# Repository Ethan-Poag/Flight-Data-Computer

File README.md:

# Flight-Data-Computer
An easy to build open source alternative to the ASA CX-3 aviation data computer.

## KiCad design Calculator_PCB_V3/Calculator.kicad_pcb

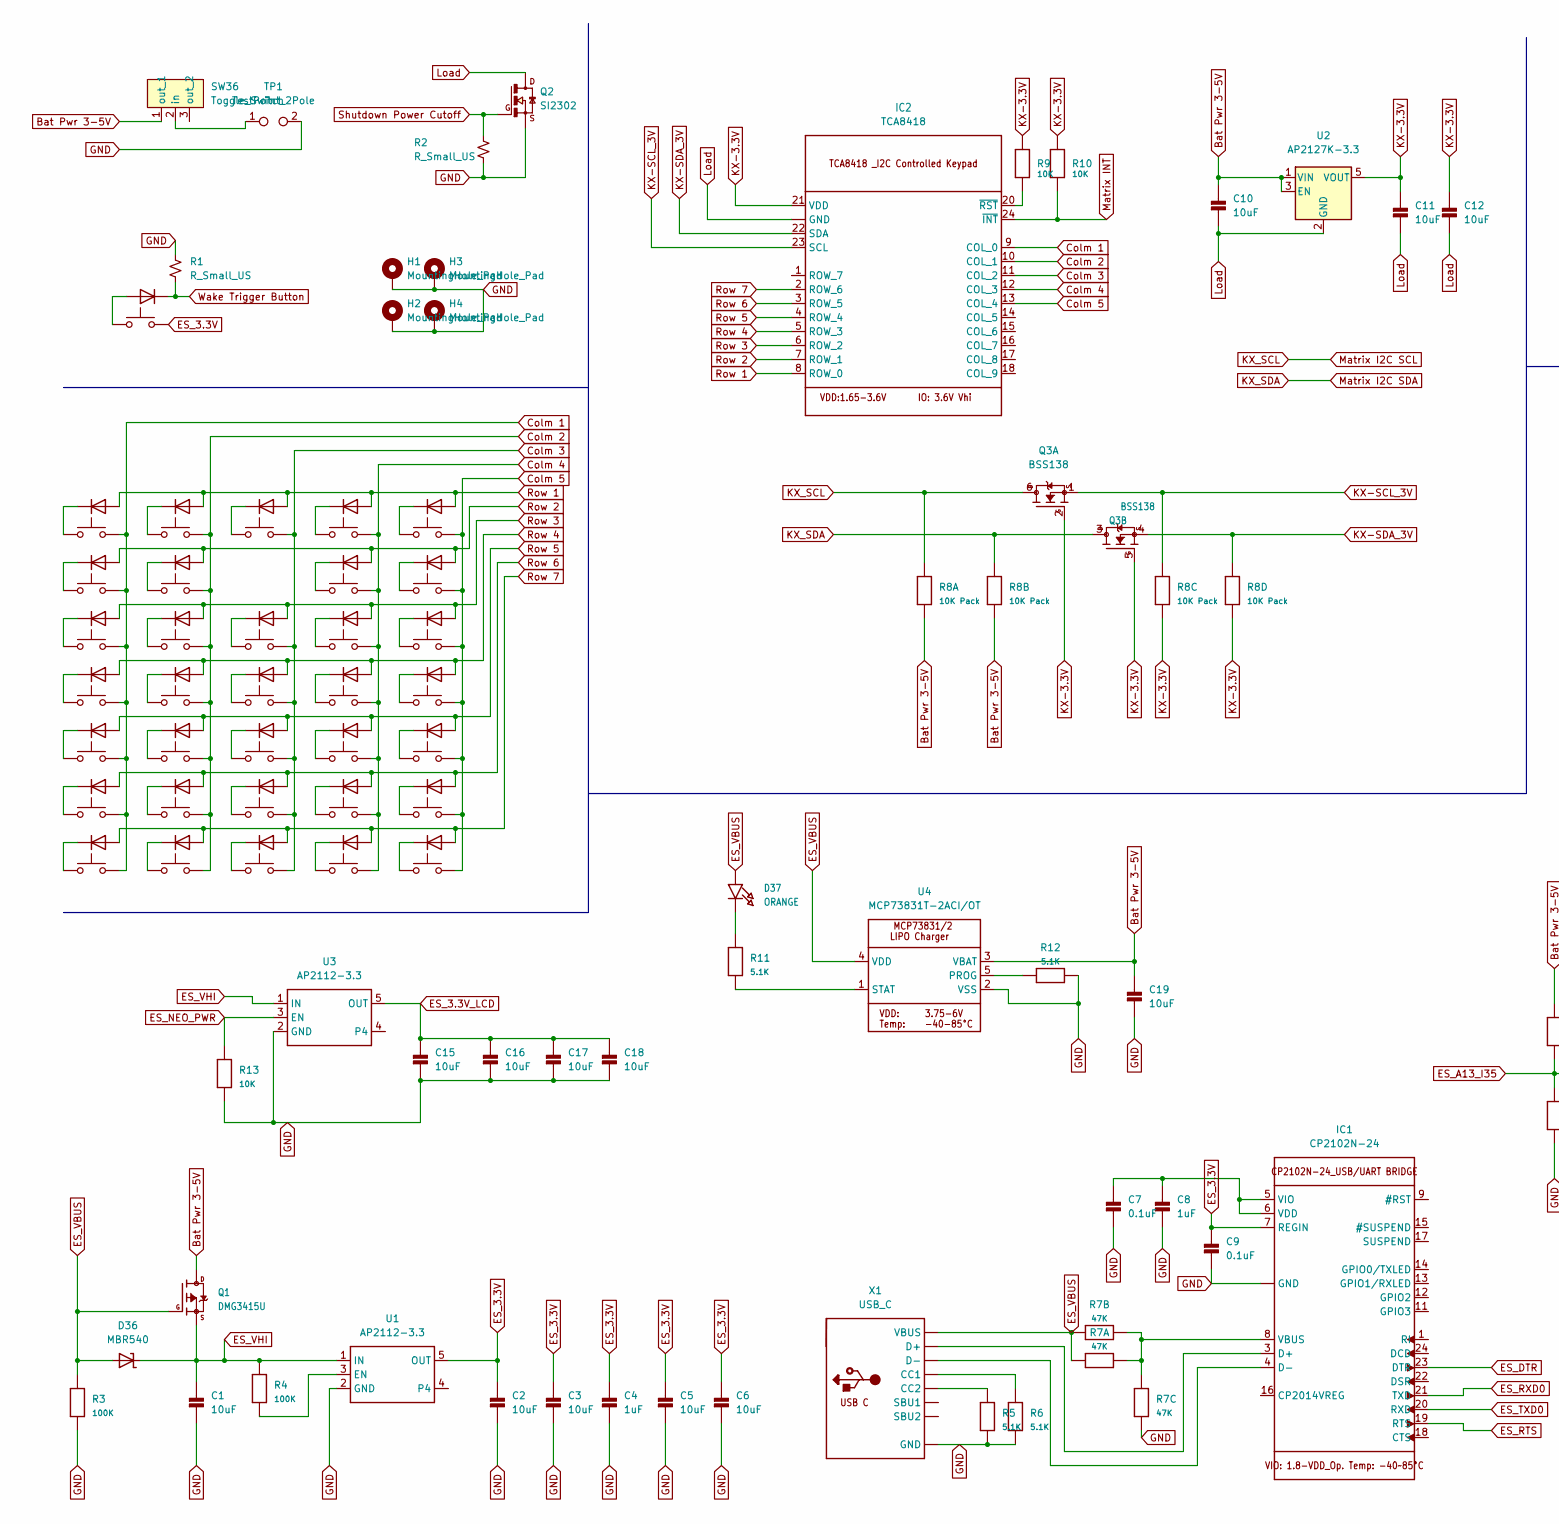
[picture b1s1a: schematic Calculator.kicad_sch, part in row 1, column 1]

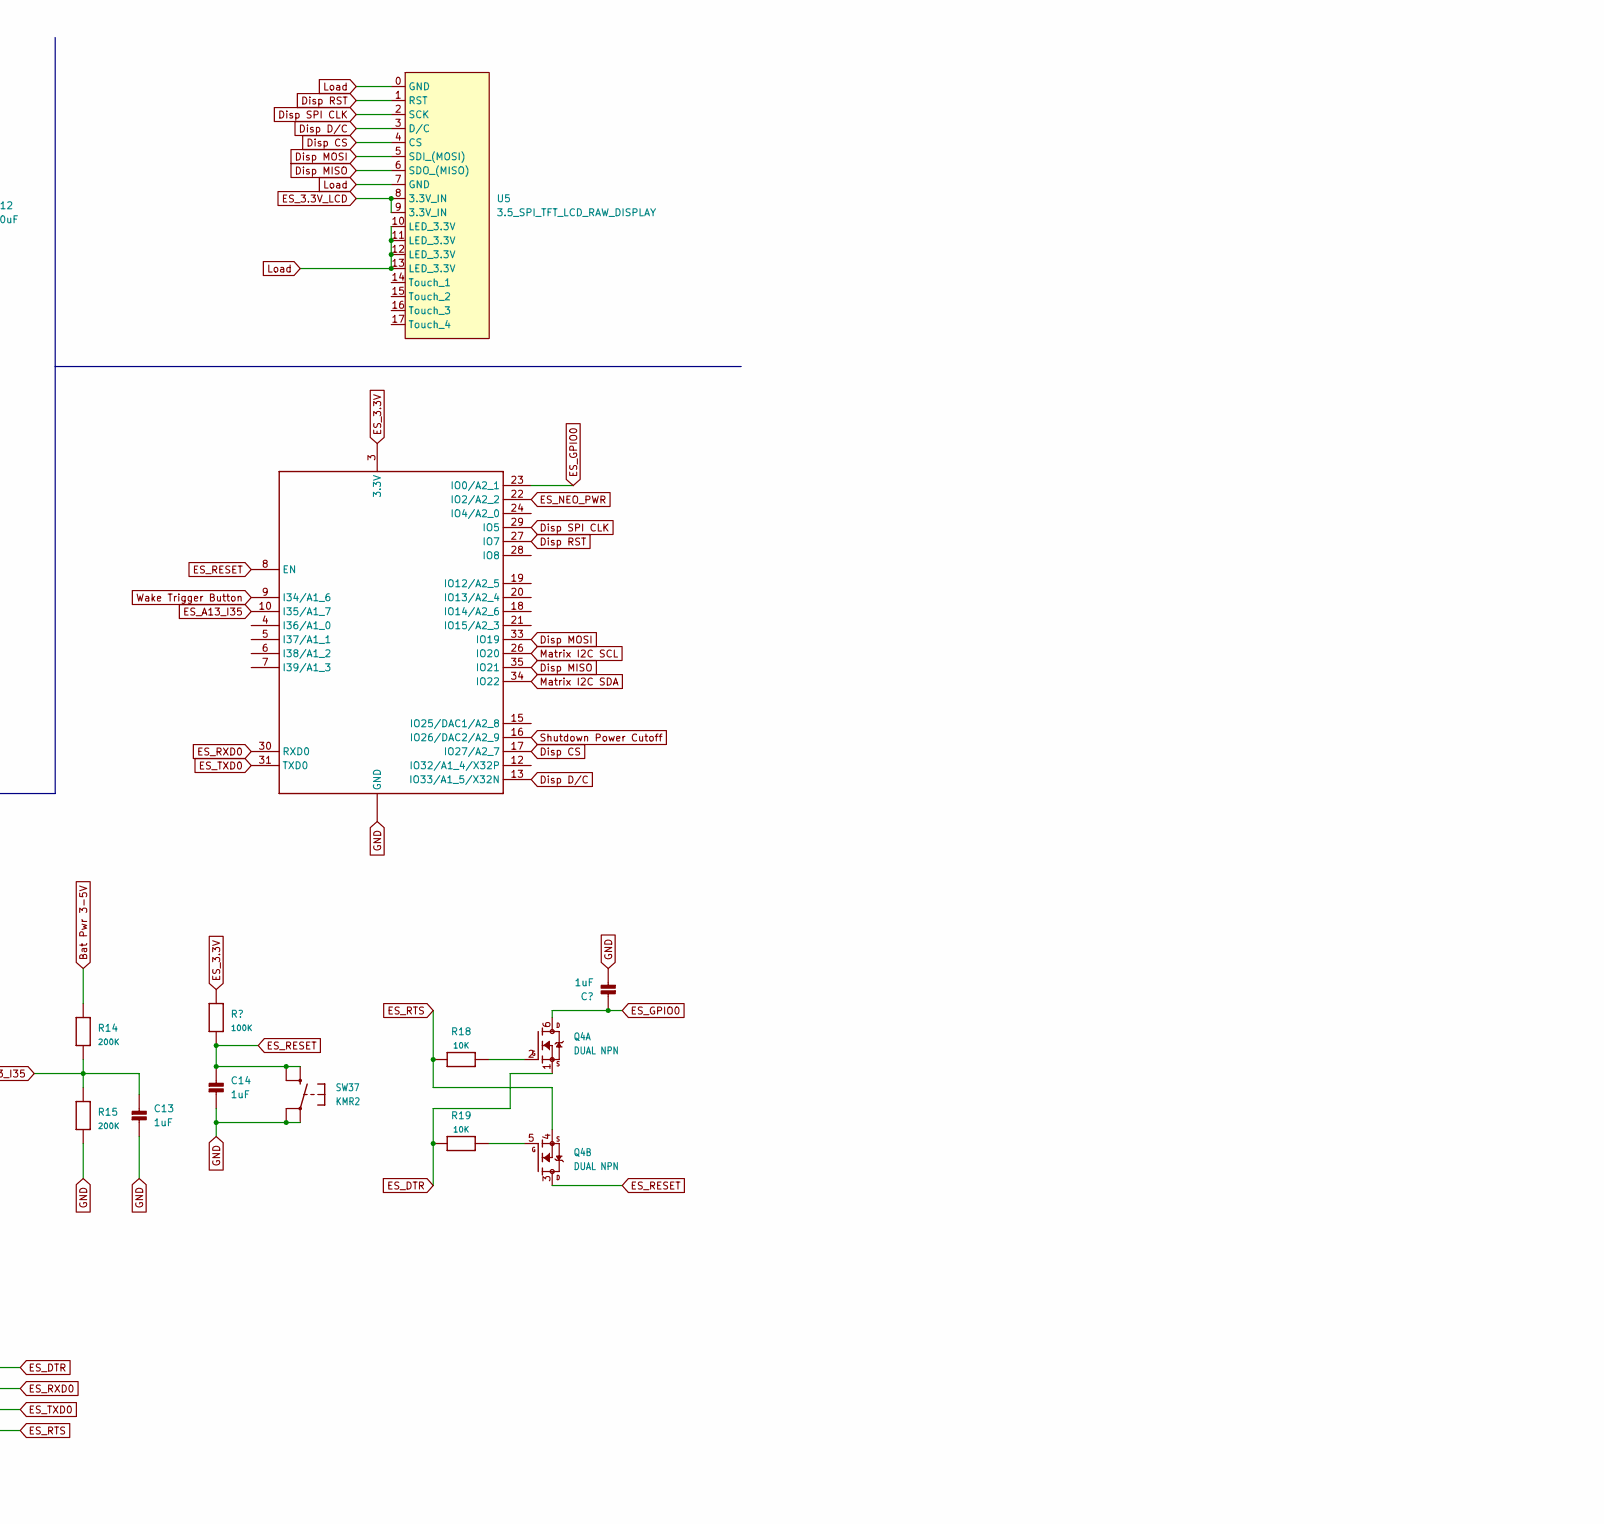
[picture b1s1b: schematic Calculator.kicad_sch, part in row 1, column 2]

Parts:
C1, C2, C3, C5, C6, C10, C11, C12, C15, C16, C17, C18, C19: 10uF; 0805-NO
C4, C8, C13, C14: 1uF; 0805-NO
C7, C9: 0.1uF; 0805-NO
D1, D2, D3, D4, D5, D6, D7, D8, D9, D10, D11, D12, D13, D14, D15, D16, D17, D18, D19, D20, D21, D22, D23, D24, D25, D26, D27, D28, D29, D30, D31, D32, D33, D34, D35: 1N4148WT; D_SOD-523
D36: MBR540; SOD-123
D37: ORANGE; CHIPLED_0603_NOOUTLINE
H1, H2, H3, H4: MountingHole_Pad; MountingHole_3.2mm_M3_Pad_Via
IC1: CP2102N-24; QFN24_4MM_SMSC
IC2: TCA8418; QFN24_4MM_SMSC
Q1: DMG3415U; SOT23-R
Q2: SI2302; SOT23
Q3: BSS138; SOT363
Q4: DUAL NPN; SOT363
R1, R2: R_Small_US; R_0402_1005Metric
R3, R4: 100K; 0603-NO
R5, R6, R11, R12: 5.1K; 0603-NO
R7: 47K; RESPACK_4X0603
R8: 10K Pack; RESPACK_4X0603
R9, R10, R13, R18, R19: 10K; 0603-NO
R14, R15: 200K; 0603-NO
SW1, SW2, SW3, SW4, SW5, SW6, SW7, SW8, SW9, SW10, SW11, SW12, SW13, SW14, SW15, SW16, SW17, SW18, SW19, SW20, SW21, SW22, SW23, SW24, SW25, SW26, SW27, SW28, SW29, SW30, SW31, SW32, SW33, SW34, SW35: SW_Push; SW_TS-1187A-B-A-B
SW36: Toggle_Switch; FanPinHeader_1x03_P2.54mm_Vertical
SW37: KMR2; BTN_KMR2_4.6X2.8
TP1: TestPoint_2Pole; Battery Solder Pad
U1, U3: AP2112-3.3; SOT23-5
U2: AP2127K-3.3; SOT-23-5
U4: MCP73831T-2ACI/OT; SOT23-5
U5: 3.5_SPI_TFT_LCD_RAW_DISPLAY
X1: USB_C; USB_C_CUSB31-CFM2AX-01-X
X2: ESP32-PICO-MINI-02MINI; ESP32-PICO-MINI

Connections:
Bat Pwr 3-5V: C10.1, C19.1, Q1.3 (D), R8.7 (2), R8.8 (2), R14.2, SW36.1 (out_1), U2.1 (VIN), U2.3 (EN), U4.3 (VBAT)
Colm 1: IC2.9 (COL_0), SW1.2, SW2.2, SW3.2, SW4.2, SW5.2, SW6.2, SW7.2
Colm 2: IC2.10 (COL_1), SW8.2, SW9.2, SW10.2, SW11.2, SW12.2, SW13.2, SW14.2
Colm 3: IC2.11 (COL_2), SW15.2, SW17.2, SW18.2, SW19.2, SW20.2, SW21.2
Colm 4: IC2.12 (COL_3), SW22.2, SW23.2, SW24.2, SW25.2, SW26.2, SW27.2, SW28.2
Colm 5: IC2.13 (COL_4), SW29.2, SW30.2, SW31.2, SW32.2, SW33.2, SW34.2, SW35.2
Disp CS: U5.4 (CS), X2.17 (IO27/A2_7)
Disp D/C: U5.3 (D/C), X2.13 (IO33/A1_5/X32N)
Disp MISO: U5.6 (SDO_(MISO)), X2.35 (IO21)
Disp MOSI: U5.5 (SDI_(MOSI)), X2.33 (IO19)
Disp RST: U5.1 (RST), X2.27 (IO7)
Disp SPI CLK: U5.2 (SCK), X2.29 (IO5)
ES_3.3V_LCD: C15.1, C16.1, C17.1, C18.1, U3.5 (OUT), U5.8 (3.3V_IN), U5.9 (3.3V_IN)
ES_A13_I35: C13.1, R14.1, R15.2, X2.10 (I35/A1_7)
ES_DTR: IC1.23 (DTR), Q4.1 (S), R19.2
ES_GPIO0: Q4.6 (D), X2.23 (IO0/A2_1)
ES_NEO_PWR: R13.2, U3.3 (EN), X2.22 (IO2/A2_2)
ES_RESET: C14.1, Q4.3 (D), SW37.B (S), SW37.B' (S1), X2.8 (EN); also elsewhere on the board
ES_RTS: IC1.19 (RTS), Q4.4 (S), R18.2
ES_RXD0: IC1.21 (TXD), X2.30 (RXD0)
ES_TXD0: IC1.20 (RXD), X2.31 (TXD0)
ES_VHI: C1.1, D36.C, Q1.2 (S), R4.1, U1.1 (IN), U3.1 (IN)
KX-3.3V: C11.1, C12.1, IC2.21 (VDD), Q3.2 (G), Q3.5 (G), R8.5 (2), R8.6 (2), R9.2, R10.2, U2.5 (VOUT)
KX-SCL_3V: IC2.23 (SCL), Q3.1 (S), R8.3 (1)
KX-SDA_3V: IC2.22 (SDA), Q3.4 (S), R8.4 (1)
KX_SCL: Q3.6 (D), R8.1, X2.26 (IO20)
KX_SDA: Q3.3 (D), R8.2 (1), X2.34 (IO22)
Matrix INT: IC2.24 (~INT), R10.1
unnamed: C7.1, C8.1, IC1.5 (VIO), IC1.6 (VDD)
unnamed: D1.1 (K), SW1.1
unnamed: D2.1 (K), SW2.1
unnamed: D3.1 (K), SW3.1
unnamed: D4.1 (K), SW4.1
unnamed: D5.1 (K), SW5.1
unnamed: D6.1 (K), SW6.1
unnamed: D7.1 (K), SW7.1
unnamed: D8.1 (K), SW8.1
unnamed: D9.1 (K), SW9.1
unnamed: D10.1 (K), SW10.1
unnamed: D11.1 (K), SW11.1
unnamed: D12.1 (K), SW12.1
unnamed: D13.1 (K), SW13.1
unnamed: D14.1 (K), SW14.1
unnamed: D15.1 (K), SW15.1
unnamed: D16.2 (A), SW16.1
unnamed: D17.1 (K), SW17.1
unnamed: D18.1 (K), SW18.1
unnamed: D19.1 (K), SW19.1
unnamed: D20.1 (K), SW20.1
unnamed: D21.1 (K), SW21.1
unnamed: D22.1 (K), SW22.1
unnamed: D23.1 (K), SW23.1
unnamed: D24.1 (K), SW24.1
unnamed: D25.1 (K), SW25.1
unnamed: D26.1 (K), SW26.1
unnamed: D27.1 (K), SW27.1
unnamed: D28.1 (K), SW28.1
unnamed: D29.1 (K), SW29.1
unnamed: D30.1 (K), SW30.1
unnamed: D31.1 (K), SW31.1
unnamed: D32.1 (K), SW32.1
unnamed: D33.1 (K), SW33.1
unnamed: D34.1 (K), SW34.1
unnamed: D35.1 (K), SW35.1
unnamed: D37.C, R11.2
unnamed: IC1.3 (D+), X1.A6 (D+), X1.B6 (D+)
unnamed: IC1.4 (D-), X1.A7 (D-), X1.B7 (D-)
unnamed: IC1.8 (VBUS), R7.6 (2), R7.7 (2), R7.8 (2)
unnamed: IC2.20 (~RST), R9.1
unnamed: Q4.2 (G), R18.1
unnamed: Q4.5 (G), R19.1
unnamed: R4.2, U1.3 (EN)
unnamed: R5.2, X1.B5 (CC2)
unnamed: R6.2, X1.A5 (CC1)
unnamed: R11.1, U4.1 (STAT)
unnamed: R12.2, U4.5 (PROG)
unnamed: SW36.2 (in), TP1.1
Row 1: D1.2 (A), D8.2 (A), D15.2 (A), D22.2 (A), D29.2 (A), IC2.8 (ROW_0)
Row 2: D2.2 (A), D9.2 (A), D23.2 (A), D30.2 (A), IC2.7 (ROW_1)
Row 3: D3.2 (A), D10.2 (A), D17.2 (A), D24.2 (A), D31.2 (A), IC2.6 (ROW_2)
Row 4: D4.2 (A), D11.2 (A), D18.2 (A), D25.2 (A), D32.2 (A), IC2.5 (ROW_3)
Row 5: D5.2 (A), D12.2 (A), D19.2 (A), D26.2 (A), D33.2 (A), IC2.4 (ROW_4)
Row 6: D6.2 (A), D13.2 (A), D20.2 (A), D27.2 (A), D34.2 (A), IC2.3 (ROW_5)
Row 7: D7.2 (A), D14.2 (A), D21.2 (A), D28.2 (A), D35.2 (A), IC2.2 (ROW_6)
Shutdown Power Cutoff: Q2.1, R2.1, X2.16 (IO26/DAC2/A2_9)
Wake Trigger Button: D16.1 (K), R1.2, X2.9 (I34/A1_6)

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
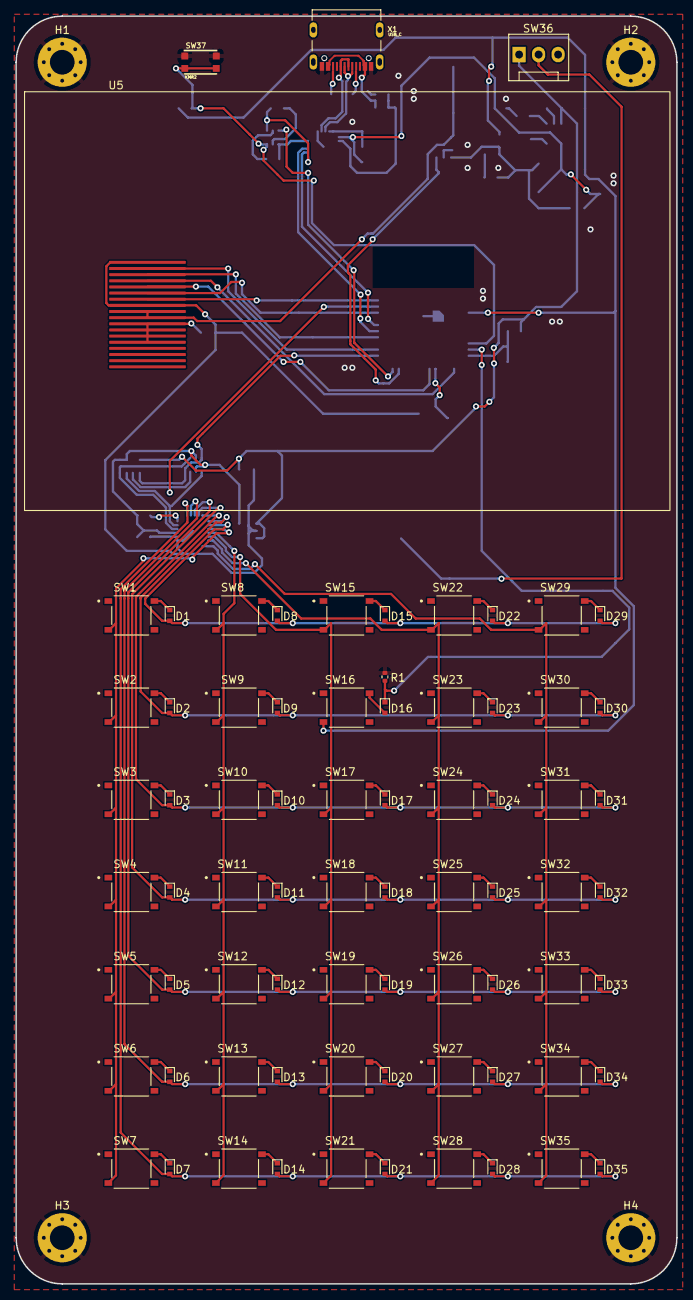
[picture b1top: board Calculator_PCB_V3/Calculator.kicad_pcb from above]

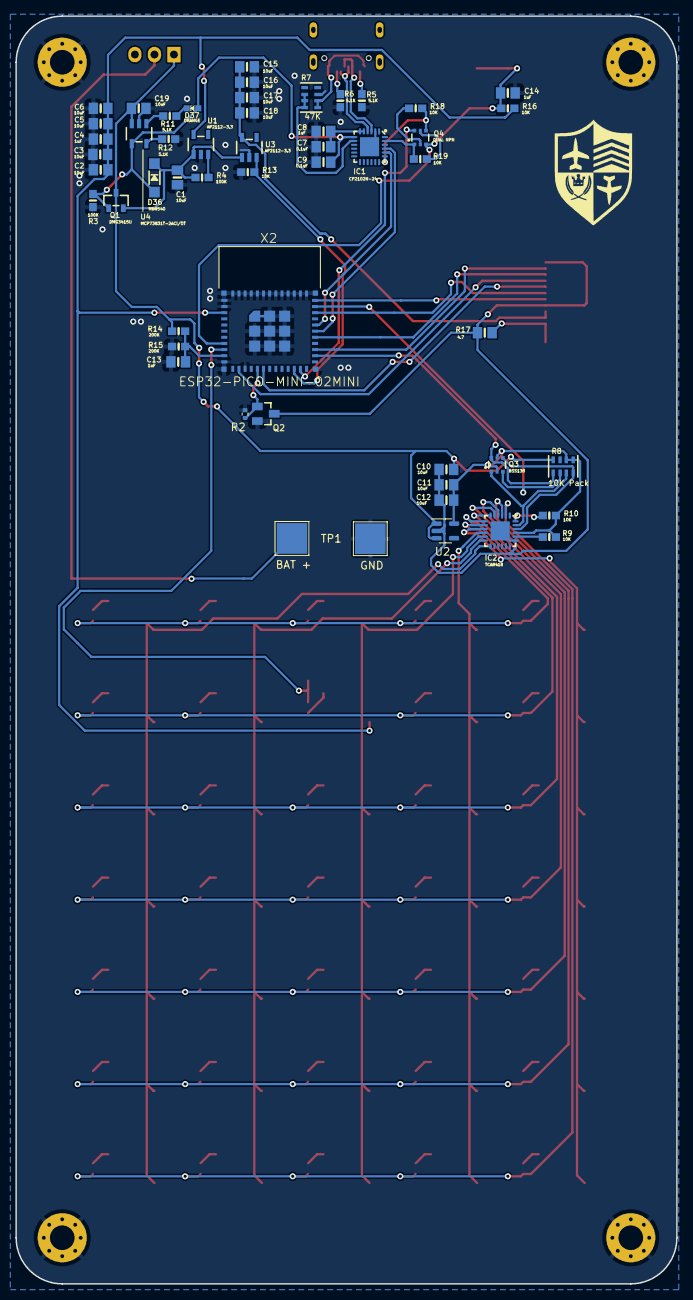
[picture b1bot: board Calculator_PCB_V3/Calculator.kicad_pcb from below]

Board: 2 copper layers, 86.0 x 165.0 mm, 130 parts (51 on the bottom side), 93 nets.

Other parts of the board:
R16: 10K; 0603-NO
R17: 4.7; 0805-NO

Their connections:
ES_RESET: R16.1; also elsewhere on the board

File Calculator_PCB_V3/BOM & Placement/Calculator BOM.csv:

Comment,Designator,Footprint,JLCPCB Part#
1N4148WT,"D3,D7,D19,D35,D17,D30,D8,D28,D2,D34,D10,D13,D32,D33,D23,D22,D9,D12,D24,D4,D16,D21,D25,D20,D11,D31,D1,D27,D18,D26,D14,D6,D15,D5,D29",D_SOD-523,C414017 
SW_Push,"SW24,SW30,SW17,SW9,SW7,SW22,SW20,SW34,SW3,SW10,SW8,SW12,SW15,SW18,SW35,SW2,SW14,SW28,SW21,SW16,SW33,SW31,SW32,SW23,SW5,SW26,SW6,SW11,SW1,SW19,SW13,SW29,SW4,SW27,SW25",SW_TS-1187A-B-A-B,C318884 
KMR2,SW37,BTN_KMR2_4.6X2.8,C99271 
USB_C,X1,USB_C_CUSB31-CFM2AX-01-X,C2765186 
R_Small_US,"R1,R2",R_0402_1005Metric,C269674 
10uF,"C5,C6,C15,C17,C19,C1,C18,C16,C3,C2,C10,C11,C12",0805-NO,C90545 
5.1K,"R11,R12,R6,R5",0603-NO,C328370 
AP2127K-3.3,U2,SOT-23-5,C156285 
100K,"R3,R4",0603-NO,C365065 
10K,"R16,R19,R18,R13,R9,R10",0603-NO,C269701 
200K,"R15,R14",0603-NO,C328345
MCP73831T-2ACI/OT,U4,SOT23-5,C424093
1uF,"C8,C14,C13,C4",0805-NO,C89190
4.7K,R17,0805-NO,C328399
DMG3415U,Q1,SOT23-R,C709946
ORANGE,D37,CHIPLED_0603_NOOUTLINE,C375450
0.1uF,"C7,C9",0805-NO,C396718
ESP32-PICO-MINI-02MINI,X2,ESP32-PICO-MINI,C2980306
DUAL NPN,Q4,SOT363,C62892
AP2112-3.3,"U1,U3",SOT23-5,C51118
SI2302,Q2,SOT23,C2891732 
47K,R7,RESPACK_4X0603,C12027
MBR540,D36,SOD-123,C8598
10K Pack,R8,RESPACK_4X0603,C29718
BSS138,Q3,SOT363,C779245
CP2102N-24,IC1,QFN24_4MM_SMSC,C969151
TCA8418,IC2,QFN24_4MM_SMSC,C138713

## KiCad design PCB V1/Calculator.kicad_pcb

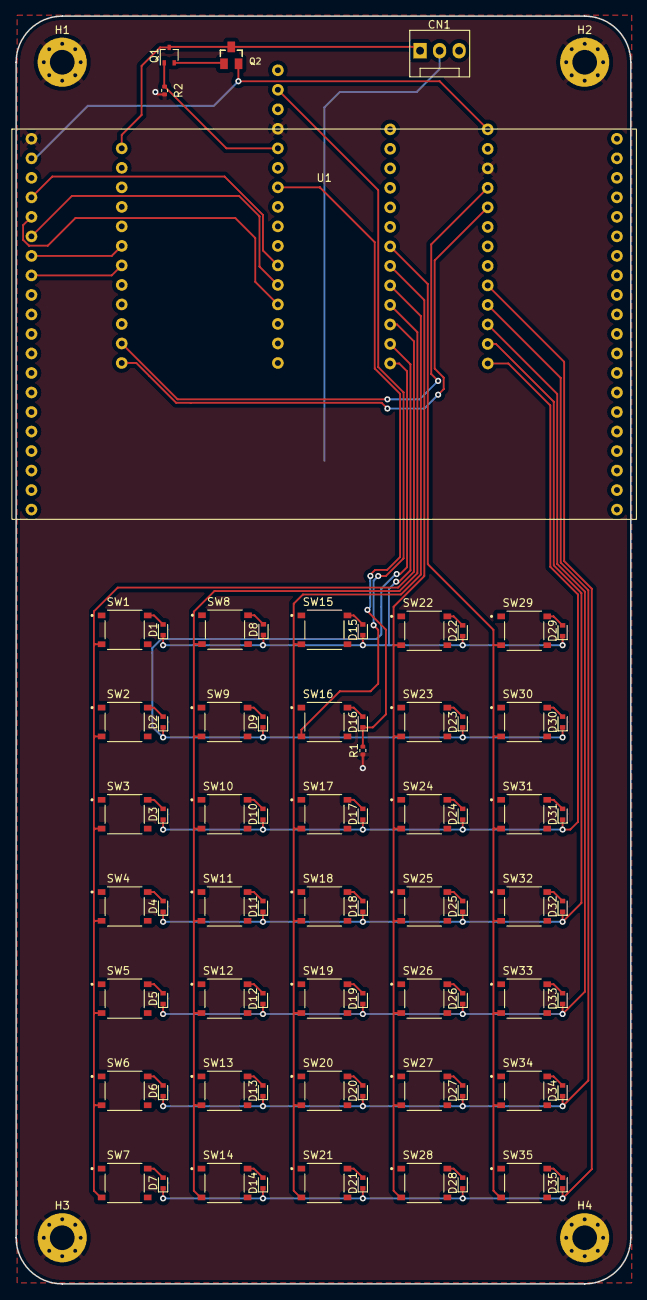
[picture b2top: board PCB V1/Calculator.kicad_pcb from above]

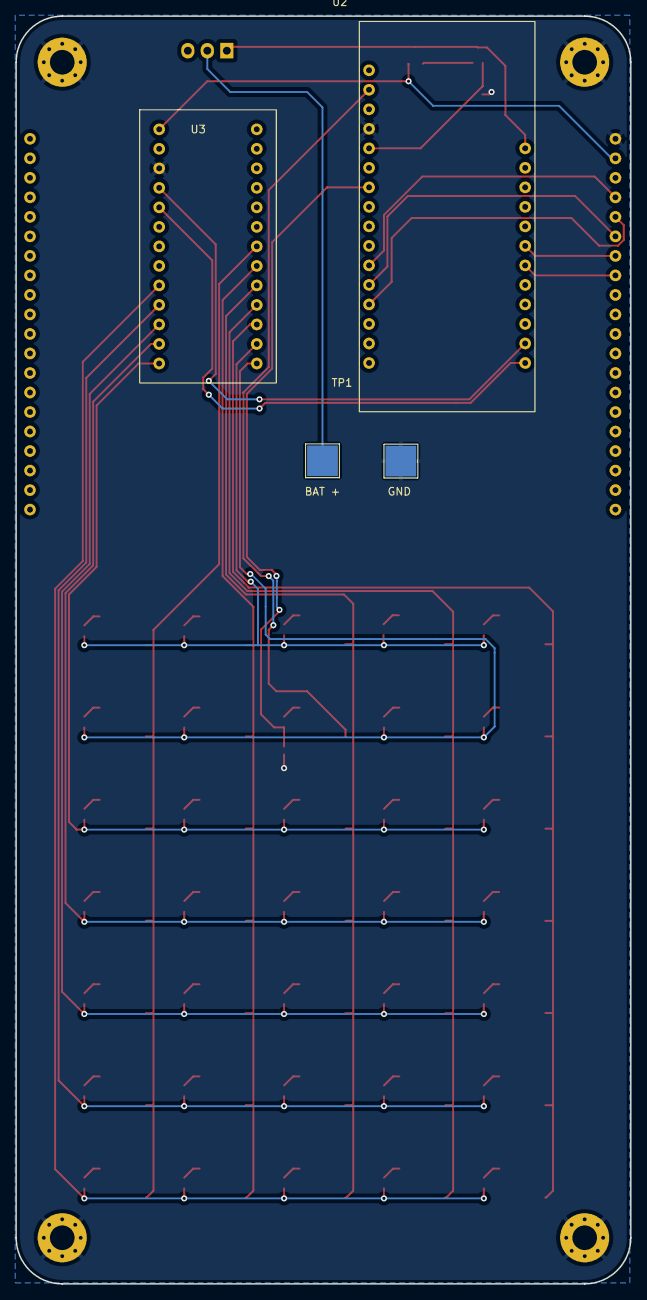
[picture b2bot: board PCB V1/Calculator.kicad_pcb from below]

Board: 2 copper layers, 80.0 x 165.0 mm, 83 parts (3 on the bottom side), 62 nets.

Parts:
CN1: Toggle_Switch; FanPinHeader_1x03_P2.54mm_Vertical
D1, D2, D3, D4, D5, D6, D7, D8, D9, D10, D11, D12, D13, D14, D15, D16, D17, D18, D19, D20, D21, D22, D23, D24, D25, D26, D27, D28, D29, D30, D31, D32, D33, D34, D35: 1N914WT; D_SOD-523
H1, H2, H3, H4: MountingHole_Pad; MountingHole_3.2mm_M3_Pad_Via
Q1: 2SC4213; SOT-323_SC-70
Q2: SI2302; SOT23
R1, R2: R_Small_US; R_0402_1005Metric
SW1, SW2, SW3, SW4, SW5, SW6, SW7, SW8, SW9, SW10, SW11, SW12, SW13, SW14, SW15, SW16, SW17, SW18, SW19, SW20, SW21, SW22, SW23, SW24, SW25, SW26, SW27, SW28, SW29, SW30, SW31, SW32, SW33, SW34, SW35: SW_Push; SW_TS-1187A-B-A-B
TP1: TestPoint_2Pole; Battery Solder Pad
U1: 2.8"_TFT_LCD_with_Touchscreen_Breakout_Board_w/Mi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; 2-8 TFT LCD with Touchscreen Breakout Board ILI9341
U2: Adafruit_ESP32_Feather_V2; Adafruit ESP32 Feather V2
U3: Adafruit_TCA8418_Keypad_Matrix_and_GPIO_Expander_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; Adafruit TCA8418 Keypad Matrix and GPIO Expander

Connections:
3-5V (ON): Q2.2, U1.18 (3-5V), U3.0 (VIN)
3V: SW16.2, U2.13 (3V)
Bat Pwr 3-5V: CN1.1 (out_1), Q1.3 (C), Q2.3, U2.0 (BAT)
Colm 1: SW1.2, SW2.2, SW3.2, SW4.2, SW5.2, SW6.2, SW7.2, U3.23 (C0)
Colm 2: SW8.2, SW9.2, SW10.2, SW11.2, SW12.2, SW13.2, SW14.2, U3.22 (C1)
Colm 3: SW15.2, SW17.2, SW18.2, SW19.2, SW20.2, SW21.2, U3.21 (C2)
Colm 4: SW22.2, SW23.2, SW24.2, SW25.2, SW26.2, SW27.2, SW28.2, U3.20 (C3)
Colm 5: SW29.2, SW30.2, SW31.2, SW32.2, SW33.2, SW34.2, SW35.2, U3.19 (C4)
Disp CS: U1.13 (CS), U2.5 (27/A10)
Disp D/C: U1.12 (D/C), U2.6 (33/A9)
Disp MISO: U1.15 (MISO), U2.24 (21/MISO)
Disp MOSI: U1.14 (MOSI), U2.23 (19/MOSI)
Disp SPI CLK: U1.16 (CLK), U2.22 (5/SCK)
GND: H1.1, H2.1, H3.1, H4.1, R1.1, R2.2, TP1.2, U1.19 (GND), U2.15 (GND), U3.2 (GND)
Matrix I2C SCL: U2.10 (SCL/20), U3.3 (SCL)
Matrix I2C SDA: U2.11 (SDA/22), U3.4 (SDA)
unnamed: D1.2 (A), SW1.1
unnamed: D2.2 (A), SW2.1
unnamed: D3.2 (A), SW3.1
unnamed: D4.2 (A), SW4.1
unnamed: D5.2 (A), SW5.1
unnamed: D6.2 (A), SW6.1
unnamed: D7.2 (A), SW7.1
unnamed: D8.2 (A), SW8.1
unnamed: D9.2 (A), SW9.1
unnamed: D10.2 (A), SW10.1
unnamed: D11.2 (A), SW11.1
unnamed: D12.2 (A), SW12.1
unnamed: D13.2 (A), SW13.1
unnamed: D14.2 (A), SW14.1
unnamed: D15.2 (A), SW15.1
unnamed: D16.2 (A), SW16.1
unnamed: D17.2 (A), SW17.1
unnamed: D18.2 (A), SW18.1
unnamed: D19.2 (A), SW19.1
unnamed: D20.2 (A), SW20.1
unnamed: D21.2 (A), SW21.1
unnamed: D22.2 (A), SW22.1
unnamed: D23.2 (A), SW23.1
unnamed: D24.2 (A), SW24.1
unnamed: D25.2 (A), SW25.1
unnamed: D26.2 (A), SW26.1
unnamed: D27.2 (A), SW27.1
unnamed: D28.2 (A), SW28.1
unnamed: D29.2 (A), SW29.1
unnamed: D30.2 (A), SW30.1
unnamed: D31.2 (A), SW31.1
unnamed: D32.2 (A), SW32.1
unnamed: D33.2 (A), SW33.1
unnamed: D34.2 (A), SW34.1
unnamed: D35.2 (A), SW35.1
unnamed: Q1.2 (E), Q2.1
unnamed: CN1.2 (in), TP1.1
Row 1: D1.1 (K), D8.1 (K), D15.1 (K), D22.1 (K), D29.1 (K), U3.24 (R0)
Row 2: D2.1 (K), D9.1 (K), D23.1 (K), D30.1 (K), U3.25 (R1)
Row 3: D3.1 (K), D10.1 (K), D17.1 (K), D24.1 (K), D31.1 (K), U3.12 (R2)
Row 4: D4.1 (K), D11.1 (K), D18.1 (K), D25.1 (K), D32.1 (K), U3.11 (R3)
Row 5: D5.1 (K), D12.1 (K), D19.1 (K), D26.1 (K), D33.1 (K), U3.10 (R4)
Row 6: D6.1 (K), D13.1 (K), D20.1 (K), D27.1 (K), D34.1 (K), U3.9 (R5)
Row 7: D7.1 (K), D14.1 (K), D21.1 (K), D28.1 (K), D35.1 (K), U3.8 (R6)
Shutdown Power Cutoff: Q1.1 (B), R2.1, U2.16 (26/A0)
Wake Trigger Button: D16.1 (K), R1.2, U2.18 (34/A2)

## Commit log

2022-11-03 Add files via upload
    Uploading the first and second prototype PCB designs.
2022-11-27 Version 3 of the calculator PCB
    Calculator PCB version 3. Everything on this PCB should be fully working as is with no modifications.
2022-11-27 3D models for the calculator
2023-01-02 Upload working code for scrolling menu
    Scrollable menu with clickable option.
